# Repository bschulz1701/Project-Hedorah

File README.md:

# Project-Hedorah
A hardened CO2 sensing system designed for use in unusual environments 

>[!NOTE]
> Manufacture and assembly information is discussed in detail in [DFM_-_Hedorah-NDIR](https://github.com/GEMS-sensing/DFM_-_Hedorah-NDIR)

# Repo Roadmap
#### [Documents](Documents/)

General document and image storage for repo and README

#### [Hardware](Hardware/)

Current board files (Eagle), and other electrical design documents

#### [Mechanical](Mechanical/)

Mechanical design files and assembly documents

#### [Production](Production/)

Contains the various Gerber and pick and place files required to have the Printed Circuit Boards (PCBs) manufactured or populated 

#### [Software](Software/)

The software associated with the piece of hardware, this is usually diagnostic software used for verifying or investigating the hardware

<!-- #### [Testing](Testing/)

Scripts and results from the testing process and development process. Contains more detailed information about documented issues among other testing. --> 

## Overview
* **Type:** Sensor
* **Interfaces:** I<sup>2</sup>C
<!-- * **Release Version:** v1.0 - 2021/04/14  -->

## Features
### On-Board
* Non-Dispersive InfraRed (NDIR) CO2 sensor - Sensirion SCD30
* IP68 rating (hardened sensor housing)

### Interface
* I<sup>2</sup>C data interface
* M12 circular connector 

<!--  -->

<picture>
  <source media="(prefers-color-scheme: dark)" srcset="Documents/Images/Pinout_LIGHT.png">
  
</picture>

## Specifications
#### Electrical
* **Input Voltage:** 3.3V
* **Sensor Current (Avg):** 19mA [^1]
* **Sensor Current (Max):** 75mA [^1]

[^1]: [SCD30 Datasheet](https://sensirion.com/media/documents/4EAF6AF8/61652C3C/Sensirion_CO2_Sensors_SCD30_Datasheet.pdf)

#### Sensor [^1]
**CO2**
* Range: 0 ~ 40,000 ppm CO2 
* Accuracy: &plusmn; 30 ppm + (3% Measured Value)
* Repeatability: &plusmn; 10 ppm

**Humidity**
* Range: 0 ~ 100%
* Accuracy: &plusmn; 3%
* Repeatability: 0.1%

**Temperature**
* Range: -40 ~ 70°C 
* Accuracy: &plusmn; (0.4°C + 0.023 x (Temperature [°C] - 25°C))
* Repeatability: &plusmn; 0.1°C

## Version History

**Mrk 0 - Prototype:** Breakout/development board for SGP30 eCO2 sensor

**Mrk 1 - eCO2:** Same components as Mrk 0, but arranged into a streamlined formfactor, compatable with [Haar](https://github.com/NorthernWidget-Skunkworks/Project-Haar) enclosure 

**Mrk 2 - NDIR:** Switched sensor to SCD30 NDIR sensor, moved away from Haar enclosure to custom enclosure

  * `v0.0` - Initial NDIR version, breakout only

  * `v1.0` - Added reverse polarity protection and I2C pullups

**Mrk 3 - Dual (BETA):** Dual sensor version with low and high range sensor

## Jumper Settings 

**Configuration Jumpers** [^2]
| Jumper | Purpose | Open | Closed | Default | 
| ------ | ------- | ---------- | ---------- | ----- | 
| `JP1` | Bypass reverse polarity protection | protection enabled | protection disabled | Open |  

[^2]: Mrk 2 only

## Known Issues/Errata

#### Vent Thread Tolerance 

**Issue:** In some cases the tolerance of the thread manufacture on the [housing body](Mechanical/HEDORAH-001_-_BetaBody/HEDORAH-001_-_BetaBody_v001.stl) can be too tight. This can be seen clearly if applying the specified torque to the vents does not screw them fully down (O-Rings making contact with the housing body). 

**Workaround:** If the issue is minor, it can be corrected by applying some plastic compatible [silicone lubricant](https://www.mcmaster.com/3025K11/) to the threads of the vent before installing - take care to only apply this to the threads and not to contaminate the vent membrane. If this is not sufficient, threads can be repaired by running an [M12x1.5mm](https://www.mcmaster.com/26015A612/) hand-tap through the holes to ensure they meet specifications.

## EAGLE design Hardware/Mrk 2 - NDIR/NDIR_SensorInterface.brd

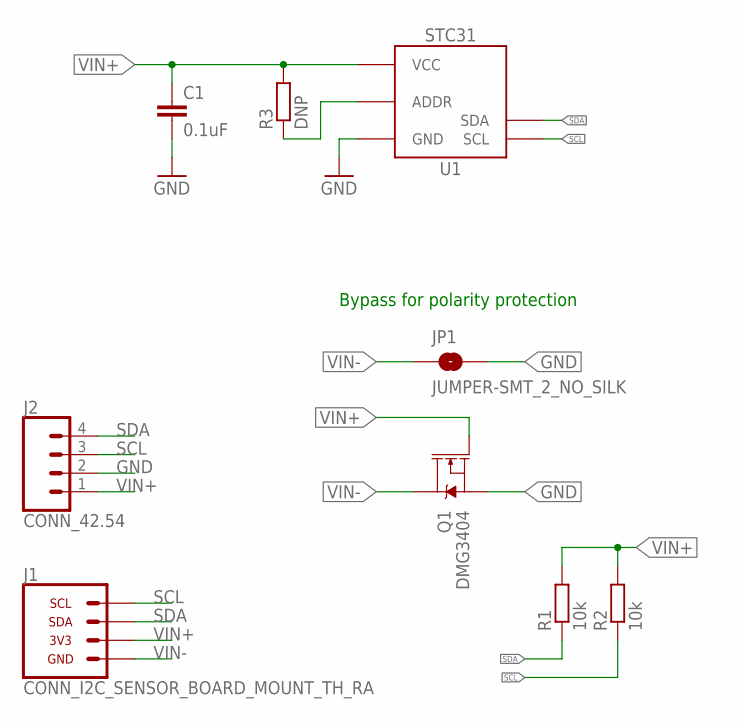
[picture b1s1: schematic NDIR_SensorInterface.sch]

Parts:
C1: 0.1uF; C0603
J1: CONN_I2C_SENSOR_BOARD_MOUNT_TH_RA; CONEC_43-01204
J2: CONN_42.54; 1X04; MPN 800-10-004-10-002000; DIGIKEY ED7564-04-ND
JP1: JUMPER-SMT_2_NO_SILK; SMT-JUMPER_2_NO_SILK
Q1: DMG3404; SOT23-3
R1, R2: 10k; R0603
R3: DNP; R0603
U1: STC31

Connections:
GND: C1.2, J2.2, JP1.2, Q1.2 (S), U1.1 (GND), U1.5 (GND), U1.9 (GND), U1.11 (GND), U1.EP (GND)
unnamed: R3.1, U1.3 (ADDR)
SCL: J1.3 (SCL), J2.3, R2.1, U1.4 (SCL)
SDA: J1.1 (SDA), J2.4, R1.1, U1.7 (SDA)
VIN+: C1.1, J1.2 (3V3), J2.1, Q1.1 (G), R1.2, R2.2, R3.2, U1.6 (VCC)
VIN-: J1.4 (GND), JP1.1, Q1.3 (D)

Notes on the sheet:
Bypass for polarity protection

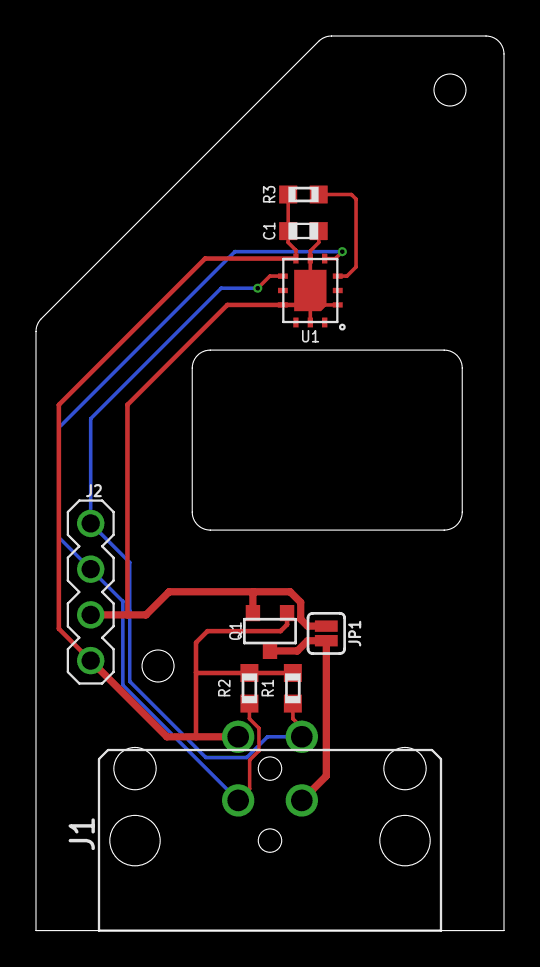
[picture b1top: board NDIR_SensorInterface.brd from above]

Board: 2 copper layers, 26.0 x 49.7 mm, 9 parts (0 on the bottom side), 6 nets.

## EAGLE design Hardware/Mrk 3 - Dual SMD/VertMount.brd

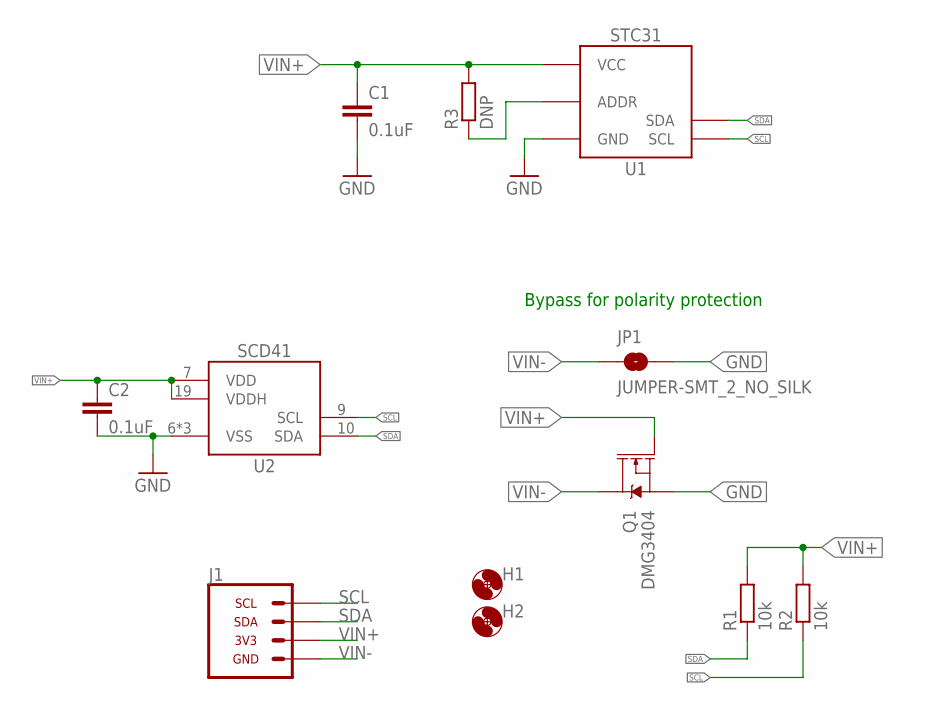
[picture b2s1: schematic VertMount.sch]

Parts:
C1, C2: 0.1uF; C0603
H1, H2: MOUNTING_HOLE1_NP; 1_72
J1: CONN_I2C_SENSOR_BOARD_MOUNT_TH; 1X04_M12_TE_T41400
JP1: JUMPER-SMT_2_NO_SILK; SMT-JUMPER_2_NO_SILK
Q1: DMG3404; SOT23-3
R1, R2: 10k; R0603
R3: DNP; R0603
U1: STC31
U2: SCD41; SCD4X

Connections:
GND: C1.2, C2.2, JP1.2, Q1.2 (S), U1.1 (GND), U1.5 (GND), U1.9 (GND), U1.11 (GND), U1.EP (GND), U2.6 (VSS), U2.20 (VSS), U2.EP (VSS)
unnamed: R3.1, U1.3 (ADDR)
SCL: J1.3 (SCL), R2.1, U1.4 (SCL), U2.9 (SCL)
SDA: J1.1 (SDA), R1.1, U1.7 (SDA), U2.10 (SDA)
VIN+: C1.1, C2.1, J1.2 (3V3), Q1.1 (G), R1.2, R2.2, R3.2, U1.6 (VCC), U2.7 (VDD), U2.19 (VDDH)
VIN-: J1.4 (GND), JP1.1, Q1.3 (D)

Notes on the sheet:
Bypass for polarity protection

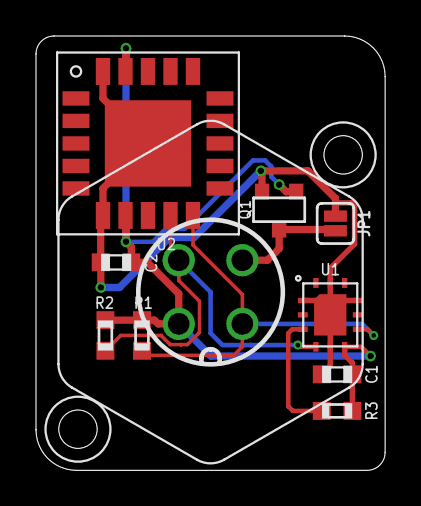
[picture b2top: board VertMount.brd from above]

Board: 2 copper layers, 19.4 x 24.1 mm, 12 parts (1 on the bottom side), 6 nets.

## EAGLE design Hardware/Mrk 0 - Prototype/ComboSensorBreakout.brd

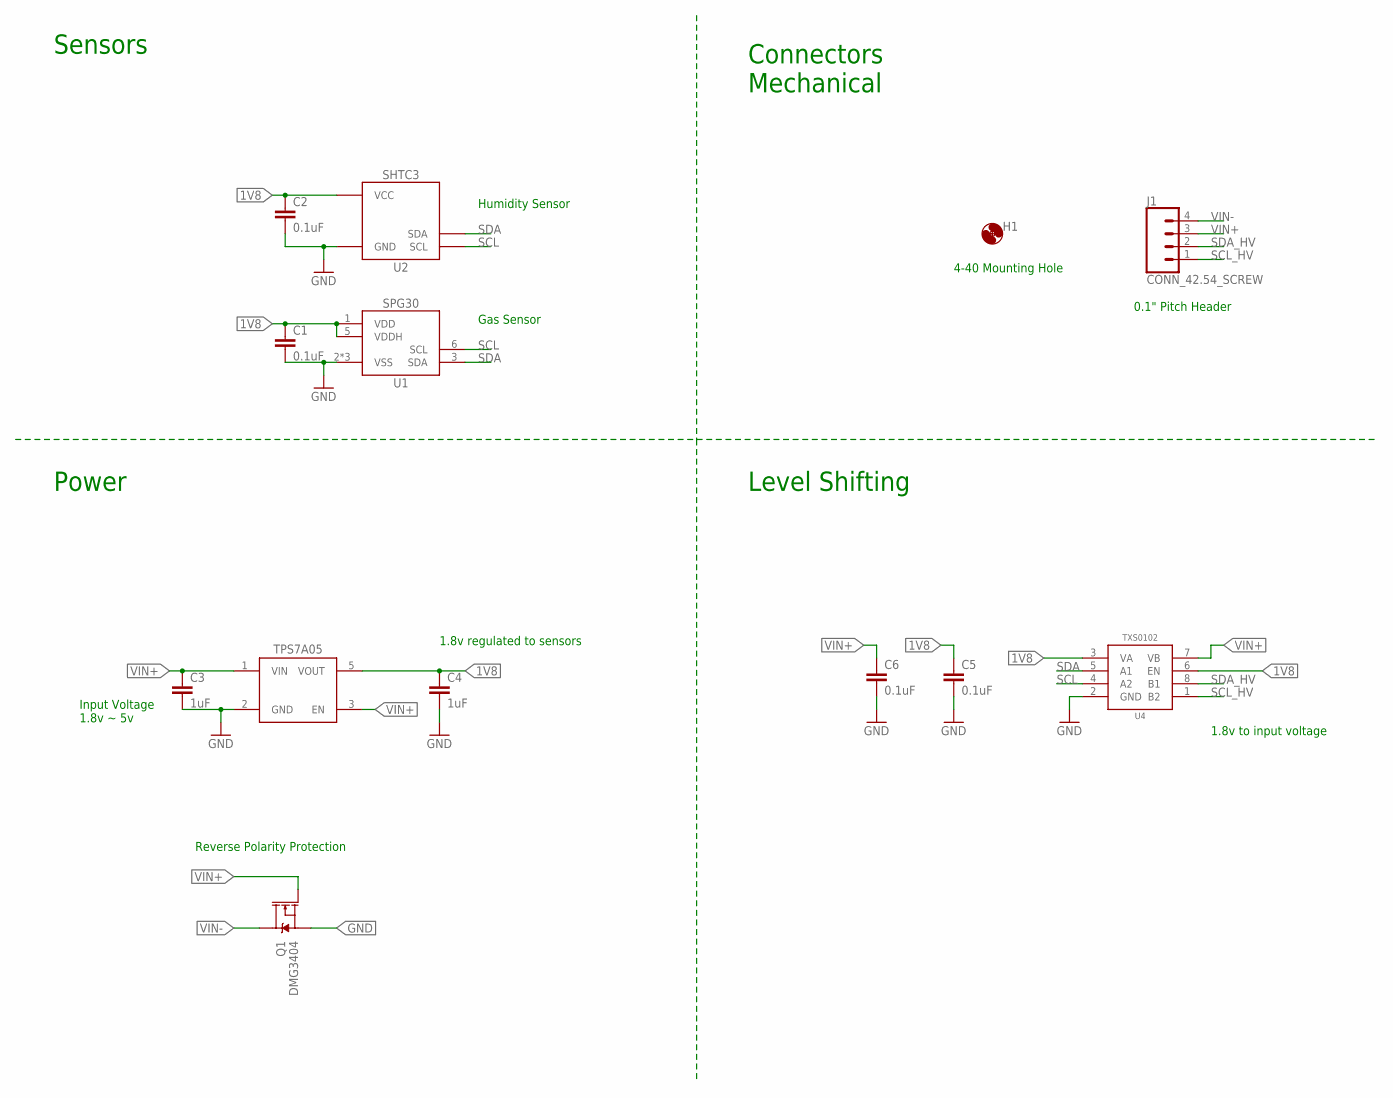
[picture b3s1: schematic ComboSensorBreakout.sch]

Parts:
C1, C2, C5, C6: 0.1uF; C0603
C3, C4: 1uF; C0603
H1: MOUNTING_HOLE4_NP; 4_40; MPN DNP; DIGIKEY DNP
J1: CONN_42.54_SCREW; 1X04_SCREW
Q1: DMG3404; SOT23-3
U1: SPG30; DFN_6_2.5X2.5
U2: SHTC3DFN; DFN_4_2X2
U3: TPS7A0518DBV; SOT23-5; DIGIKEY 296-50251-1-ND
U4: TXS0102DCU; DCU_(R-PDSO-G8)

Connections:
1V8: C1.1, C2.1, C4.1, C5.1, U1.1 (VDD), U1.5 (VDDH), U2.1 (VCC), U3.5 (VOUT), U4.3 (VA), U4.6 (EN)
GND: C1.2, C2.2, C3.2, C4.2, C5.2, C6.2, Q1.2 (S), U1.2 (VSS), U1.4 (VSS), U1.EP (VSS), U2.4 (GND), U2.EP (GND), U3.2 (GND), U4.2 (GND)
SCL: U1.6 (SCL), U2.2 (SCL), U4.4 (A2)
SCL_HV: J1.1, U4.1 (B2)
SDA: U1.3 (SDA), U2.3 (SDA), U4.5 (A1)
SDA_HV: J1.2, U4.8 (B1)
VIN+: C3.1, C6.1, J1.3, Q1.1 (G), U3.1 (VIN), U3.3 (EN), U4.7 (VB)
VIN-: J1.4, Q1.3 (D)

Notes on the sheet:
Sensors
Connectors Mechanical
Level Shifting
Power
Input Voltage 1.8v ~ 5v
1.8v regulated to sensors
Gas Sensor
Humidity Sensor
1.8v to input voltage
4-40 Mounting Hole
0.1" Pitch Header
Reverse Polarity Protection

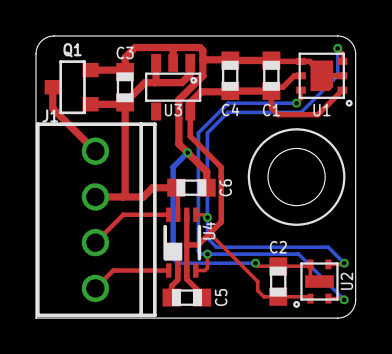
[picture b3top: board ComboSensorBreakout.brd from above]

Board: 2 copper layers, 17.8 x 15.7 mm, 13 parts (0 on the bottom side), 8 nets.

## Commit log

2019-05-13 Added license
2019-05-13 Combo sensor v0 ready for external review
    Completed initial design and documentation for combo sensor v0.0
2019-05-13 Added dimensions to board document
2020-02-22 Generated x274 gerber files
2020-03-13 Updated silk screen (fixed issue #1)
    Switched silk screen labels to be correct for Vin+/-
2020-09-28 Added initial dev for hard mounted sensor design
    Review and cleanup of layout required
2020-09-28 Minor cleanup
2021-03-30 Preliminary board layout for Hedorah-NDIR
    Layout for interface board for NDIR (SCD30 Sensor) Hedorah
2021-03-30 Fixed hole placement
    Adjusted the placement of the holes and cutout to fix errors
2021-08-03 Added demo Particle interface
2024-08-12 Updated NDIR interface board to v1.0
    Added reverse polarity protection and I2C pull up resistors
2024-08-12 Moved files into new folder structure
2024-08-12 Added mechanical parts
2024-08-12 Updated README
    Added images, pinouts, and detailed description to README
2024-08-22 Updated pinout in README
    Added support for dark and light mode support on pinout graphic
2024-08-27 Rearranged folders for version separation, software, production
    Added clear separation in hardware and production, dividing the files by version. Also moved demo code into software folder
2024-08-27 Updated/generated BoMs if not present
2024-08-27 Updated README to reflect changes
2024-08-27 Added DOI to README
2024-09-26 Mrk 3 prelim board design
    Added design for Mrk 3 sensor version
2024-09-26 Added mechanical design for Mrk 3 sensor enclosure
2024-09-26 Fixed production version naming of Mrk 2 design
    Added layout dimensions
2024-11-02 Added graphics and mechanical parts

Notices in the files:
parts and their libraries:
bschulz: This work is licensed under the Creative Commons Attribution-ShareAlike 4.0
http://creativecommons.org/licenses/by-sa/4.0
